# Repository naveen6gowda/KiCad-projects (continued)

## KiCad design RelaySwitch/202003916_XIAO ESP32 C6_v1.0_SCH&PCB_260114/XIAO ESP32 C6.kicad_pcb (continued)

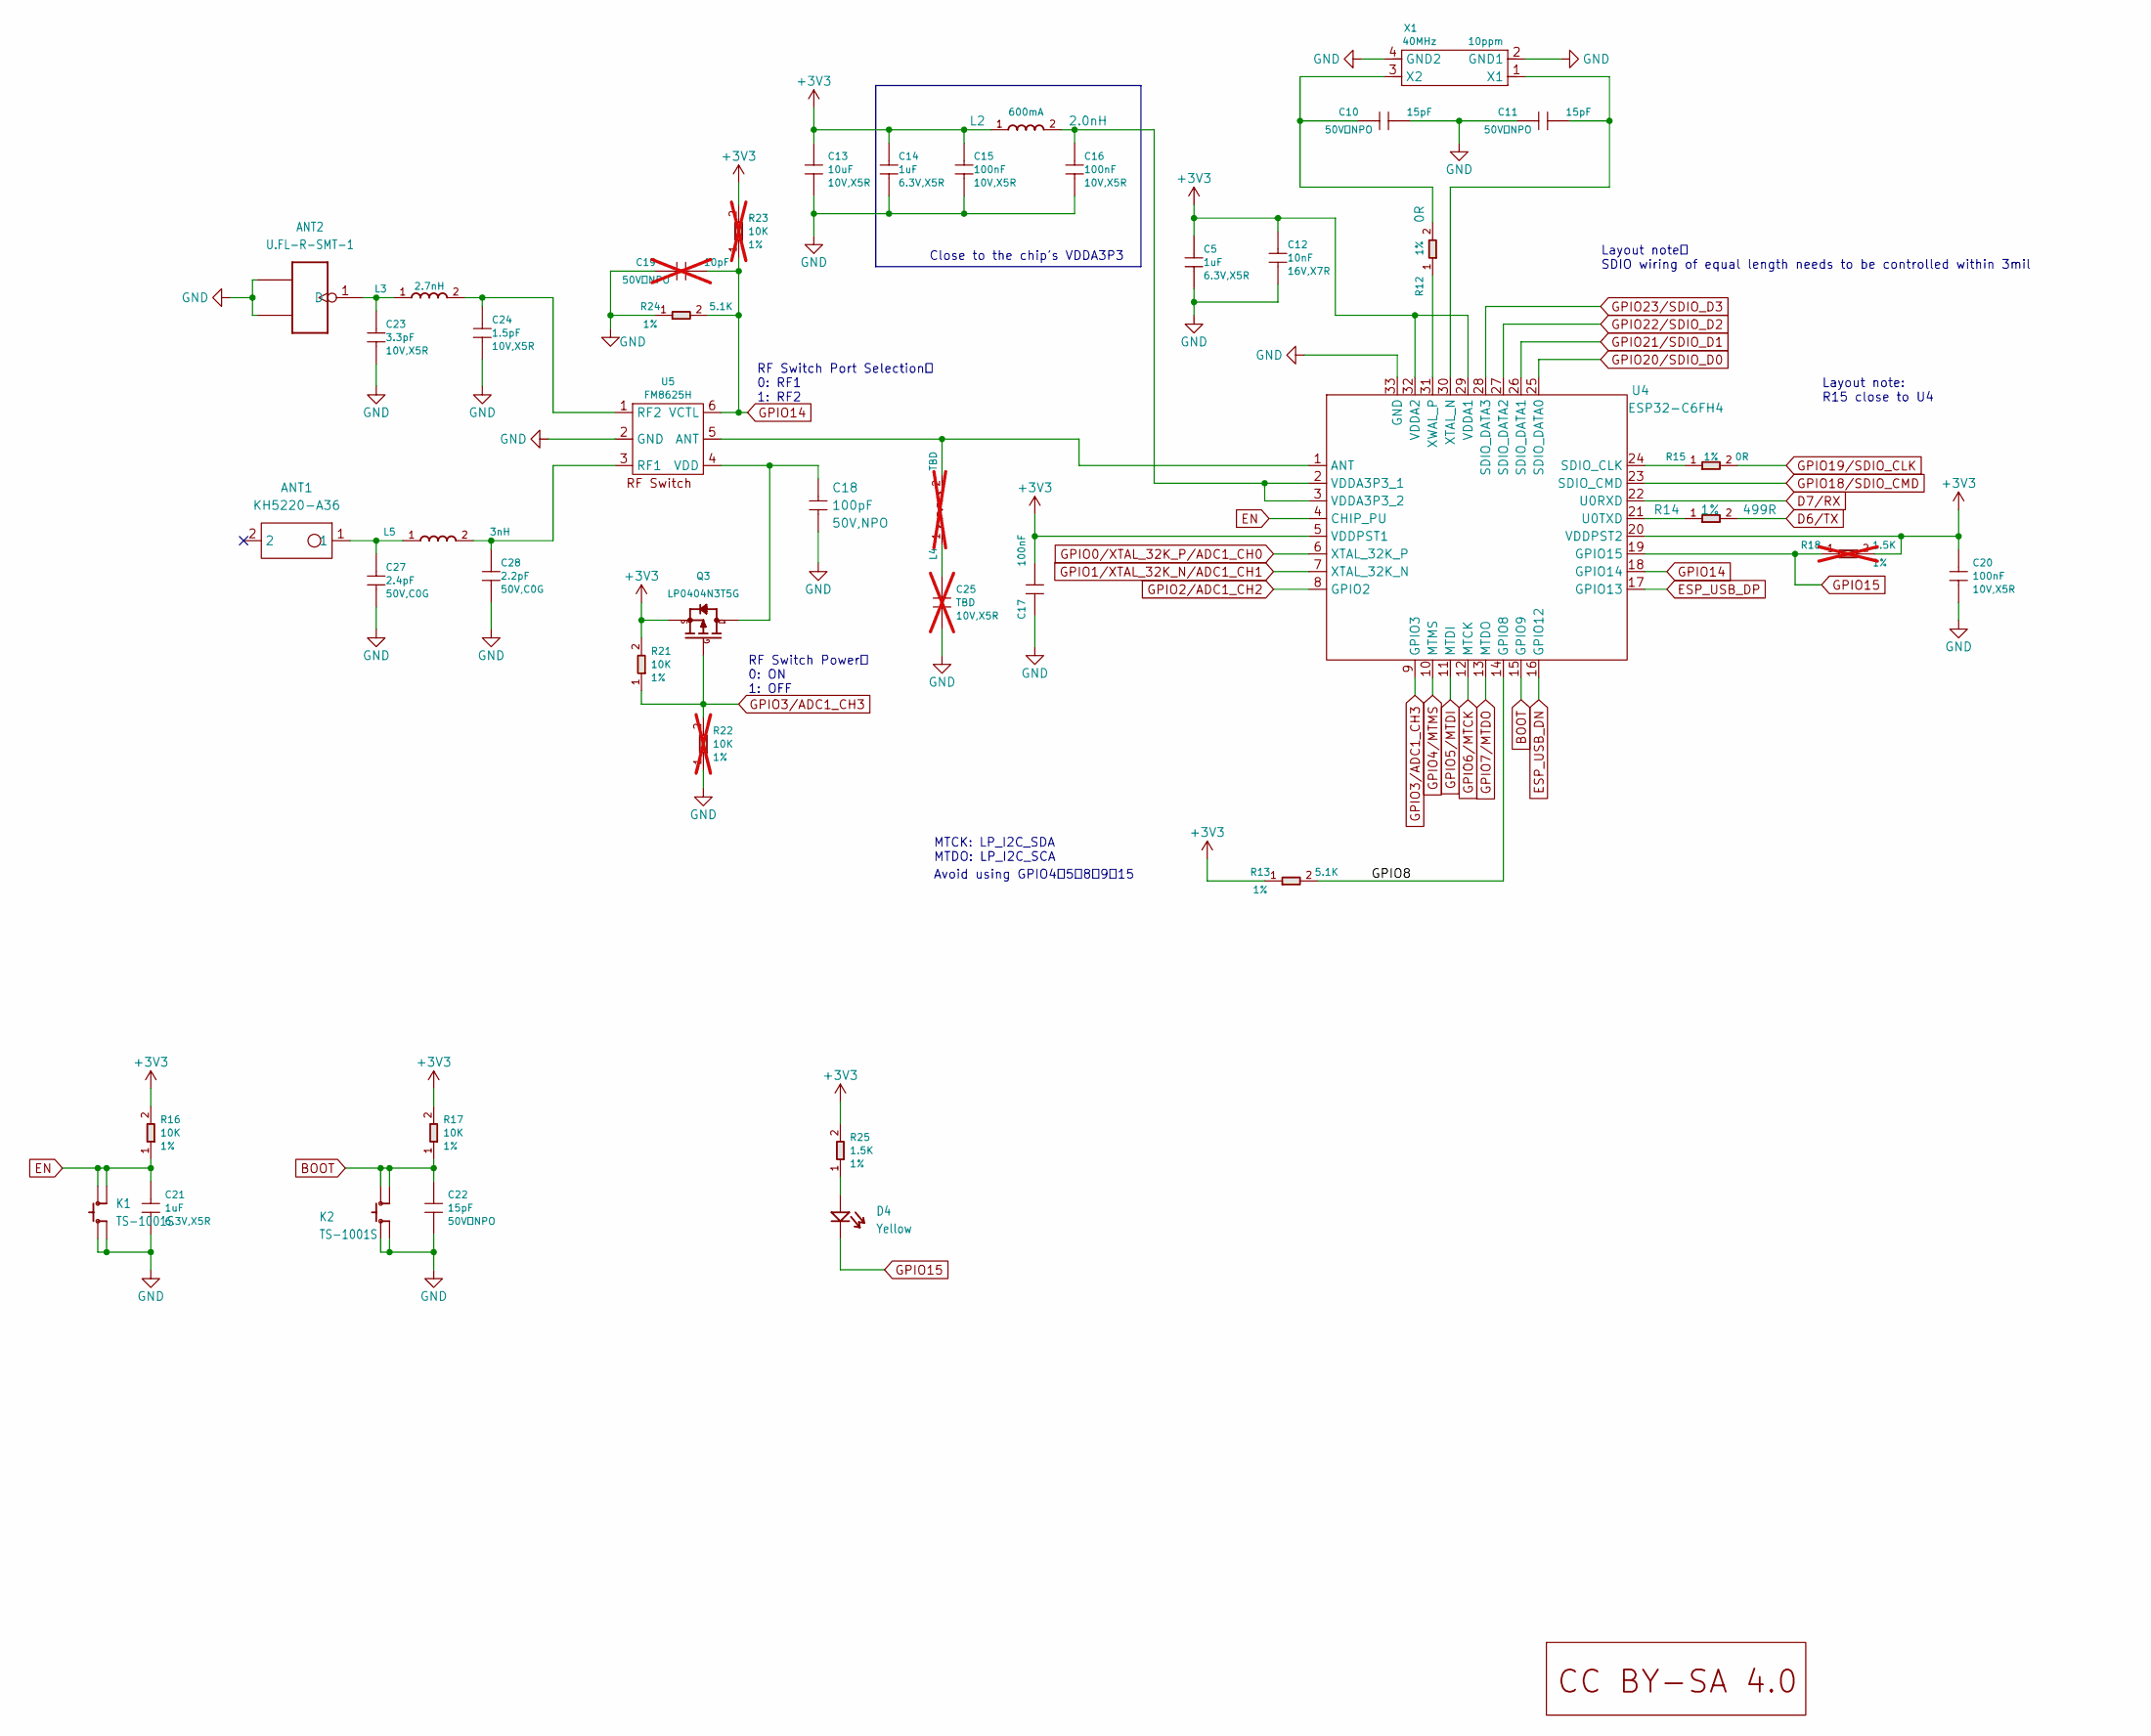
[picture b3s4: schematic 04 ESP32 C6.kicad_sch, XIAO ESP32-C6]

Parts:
ANT1: KH5220-A36; ANT2P-5.2x2x1.1MM; MPN KH5220-A36
ANT2: U.FL-R-SMT-1; U-FL3P-SMD-2.6X2.6X1.0MM; MPN U.FL-R-SMT-1
C5, C14, C21: 1uF; C0201; Voltage Rating 6.3V,X5R; MPN CC0201MRX5R5BB105
C10, C11, C22: 15pF; C0201; Voltage Rating 50V，NPO; MPN CC0201JRNPO9BN150
C12: 10nF; C0201; Voltage Rating 16V,X7R; MPN CC0201KRX7R7BB103
C13: 10uF; C0402; Voltage Rating 10V,X5R; MPN CC0402MRX5R6BB106
C15, C16, C17, C20: 100nF; C0201; Voltage Rating 10V,X5R; MPN CC0201KRX5R6BB104
C18: 100pF; C0201; Voltage Rating 50V,NPO; MPN CC0201JRNPO9BN101
C19: 10pF; C0201; Voltage Rating 50V，NPO; MPN CC0201JRNPO8BN100; not fitted
C23: 3.3pF; C0201; Voltage Rating 10V,X5R; MPN CQ0201BRNPO8BN3R3
C24: 1.5pF; C0201; Voltage Rating 10V,X5R; MPN CC0201BRNPO9BN1R5
C25: TBD; C0201; Voltage Rating 10V,X5R; Part Type Ceramic; not fitted
C27: 2.4pF; C0201; Voltage Rating 50V,C0G; MPN GRM0335C1H2R4BA01D
C28: 2.2pF; C0201; Voltage Rating 50V,C0G; MPN GRM0335C1H2R2BA01D
D4: Yellow; LED-0402; MPN 16-213/Y2C-AN2Q1B/3T
K1, K2: TS-1001S; SW4-SMD-2.8-2.6X1.6X0.53MM; MPN TS-1001S
L2: 2.0nH; L0201; Rating 600mA; MPN LQP03HQ2N0B02D
L3: 2.7nH; L0201; MPN LQP03TN2N7B02D
L4: TBD; L0201; Part Type L; not fitted
L5: 3nH; L0201; MPN LQP03TN3N0B02D
Q3: LP0404N3T5G; PMOS_1.0X0.6X0.35MM; MPN LP0404N3T5G
R12, R15: 0R; R0201; Power Rating 1%; MPN RC0201FR-070RL
R13, R24: 5.1K; R0201; Power Rating 1%; MPN RC0201FR-075K1L
R14: 499R; R0201; Power Rating 1%; MPN RC0201FR-07499RL
R16, R17, R21: 10K; R0201; Power Rating 1%; MPN RC0201FR-0710KL
R18: 1.5K; R0201; Power Rating 1%; MPN RC0201FR-071K5L; not fitted
R22, R23: 10K; R0201; Power Rating 1%; MPN RC0201FR-0710KL; not fitted
R25: 1.5K; R0201; Power Rating 1%; MPN RC0201FR-071K5L
U4: ESP32-C6FH4; QFN32-0.5-5X5MM; MPN ESP32-C6FH4
U5: FM8625H; DFN6-0.4-1.1X0.7X0.45MM; MPN FM8625H
U10: LOGO_CC_BY-SA_4.0
X1: 40MHz; X4-SMD-1.6X1.2MM; Rating 10ppm; MPN CJ17-400001010B20

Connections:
+3V3: C5.1, C12.1, C13.1, C14.1, C15.1, C17.1, C20.1, L2.1, Q3.2 (S), R13.1, R16.2, R17.2, R18.2, R21.2, R23.2, R25.2, U4.5 (VDDPST1), U4.20 (VDDPST2), U4.29 (VDDA1), U4.32 (VDDA2); also elsewhere on the board
/04 ESP32 C6/GPIO8: R13.2, U4.14 (GPIO8)
BOOT: C22.1, K2.3 (B0), K2.4 (B1), R17.1, U4.15 (GPIO9); also elsewhere on the board
D6/TX: R14.2; also elsewhere on the board
D7/RX: U4.22 (U0RXD); also elsewhere on the board
EN: C21.1, K1.3 (B0), K1.4 (B1), R16.1, U4.4 (CHIP_PU); also elsewhere on the board
ESP_USB_DN: U4.16 (GPIO12); also elsewhere on the board
ESP_USB_DP: U4.17 (GPIO13); also elsewhere on the board
GND: ANT2.2 (GND1), ANT2.3 (GND2), C5.2, C10.2, C11.1, C12.2, C13.2, C14.2, C15.2, C16.2, C17.2, C18.2, C19.1, C20.2, C21.2, C22.2, C23.2, C24.2, C25.2, C27.2, C28.2, K1.1 (A0), K1.2 (A1), K2.1 (A0), K2.2 (A1), R22.1, R24.1, U4.33 (GND), U5.2 (GND), X1.2 (GND1), X1.4 (GND2); also elsewhere on the board
GPIO0/XTAL_32K_P/ADC1_CH0: U4.6 (XTAL_32K_P); also elsewhere on the board
GPIO1/XTAL_32K_N/ADC1_CH1: U4.7 (XTAL_32K_N); also elsewhere on the board
GPIO2/ADC1_CH2: U4.8 (GPIO2); also elsewhere on the board
GPIO3/ADC1_CH3: Q3.1 (G), R21.1, R22.2, U4.9 (GPIO3)
GPIO4/MTMS: U4.10 (MTMS); also elsewhere on the board
GPIO5/MTDI: U4.11 (MTDI); also elsewhere on the board
GPIO6/MTCK: U4.12 (MTCK); also elsewhere on the board
GPIO7/MTDO: U4.13 (MTDO); also elsewhere on the board
GPIO14: C19.2, R23.1, R24.2, U4.18 (GPIO14), U5.6 (VCTL)
GPIO15: D4.2 (-), R18.1, U4.19 (GPIO15)
GPIO18/SDIO_CMD: U4.23 (SDIO_CMD); also elsewhere on the board
GPIO19/SDIO_CLK: R15.2; also elsewhere on the board
GPIO20/SDIO_D0: U4.25 (SDIO_DATA0); also elsewhere on the board
GPIO21/SDIO_D1: U4.26 (SDIO_DATA1); also elsewhere on the board
GPIO22/SDIO_D2: U4.27 (SDIO_DATA2); also elsewhere on the board
GPIO23/SDIO_D3: U4.28 (SDIO_DATA3); also elsewhere on the board
unnamed: ANT1.1, C27.1, L5.1
unnamed: ANT2.1 (D), C23.1, L3.1
unnamed: C25.1, L4.1
unnamed: D4.1 (+), R25.1
unnamed: C18.1, Q3.3 (D), U5.4 (VDD)
unnamed: L4.2, U4.1 (ANT), U5.5 (ANT)
unnamed: R15.1, U4.24 (SDIO_CLK)
unnamed: R14.1, U4.21 (U0TXD)
unnamed: C16.1, L2.2, U4.2 (VDDA3P3_1), U4.3 (VDDA3P3_2)
unnamed: C11.2, U4.30 (XTAL_N), X1.1 (X1)
unnamed: R12.1, U4.31 (XWAL_P)
unnamed: C28.1, L5.2, U5.3 (RF1)
unnamed: C24.1, L3.2, U5.1 (RF2)
unnamed: C10.1, R12.2, X1.3 (X2)

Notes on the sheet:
Avoid using GPIO4、5、8、9、15
RF Switch Power： 0: ON 1: OFF
Layout note: R15 close to U4
Close to the chip's VDDA3P3
Layout note： SDIO wiring of equal length needs to be controlled within 3mil
RF Switch Port Selection： 0: RF1 1: RF2
MTCK: LP_I2C_SDA MTDO: LP_I2C_SCA

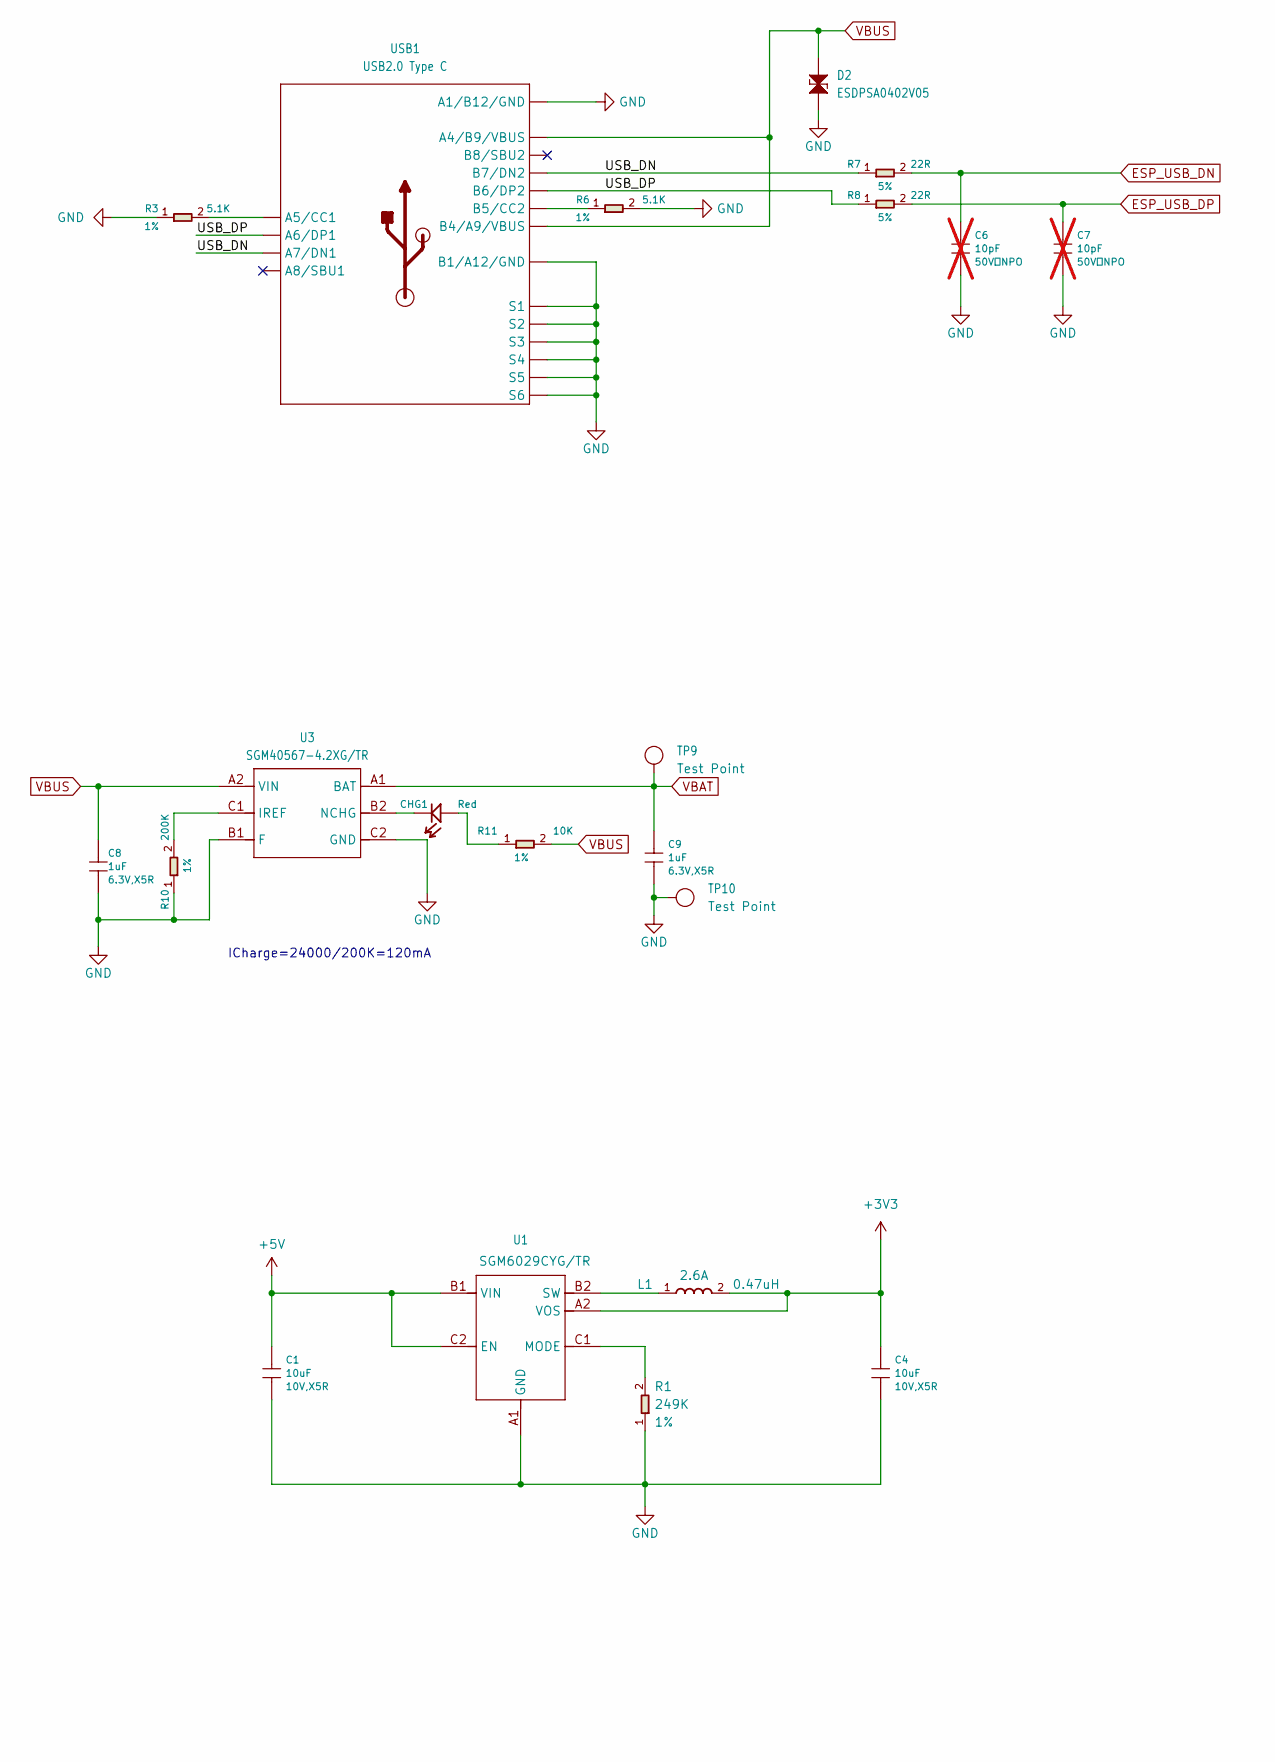
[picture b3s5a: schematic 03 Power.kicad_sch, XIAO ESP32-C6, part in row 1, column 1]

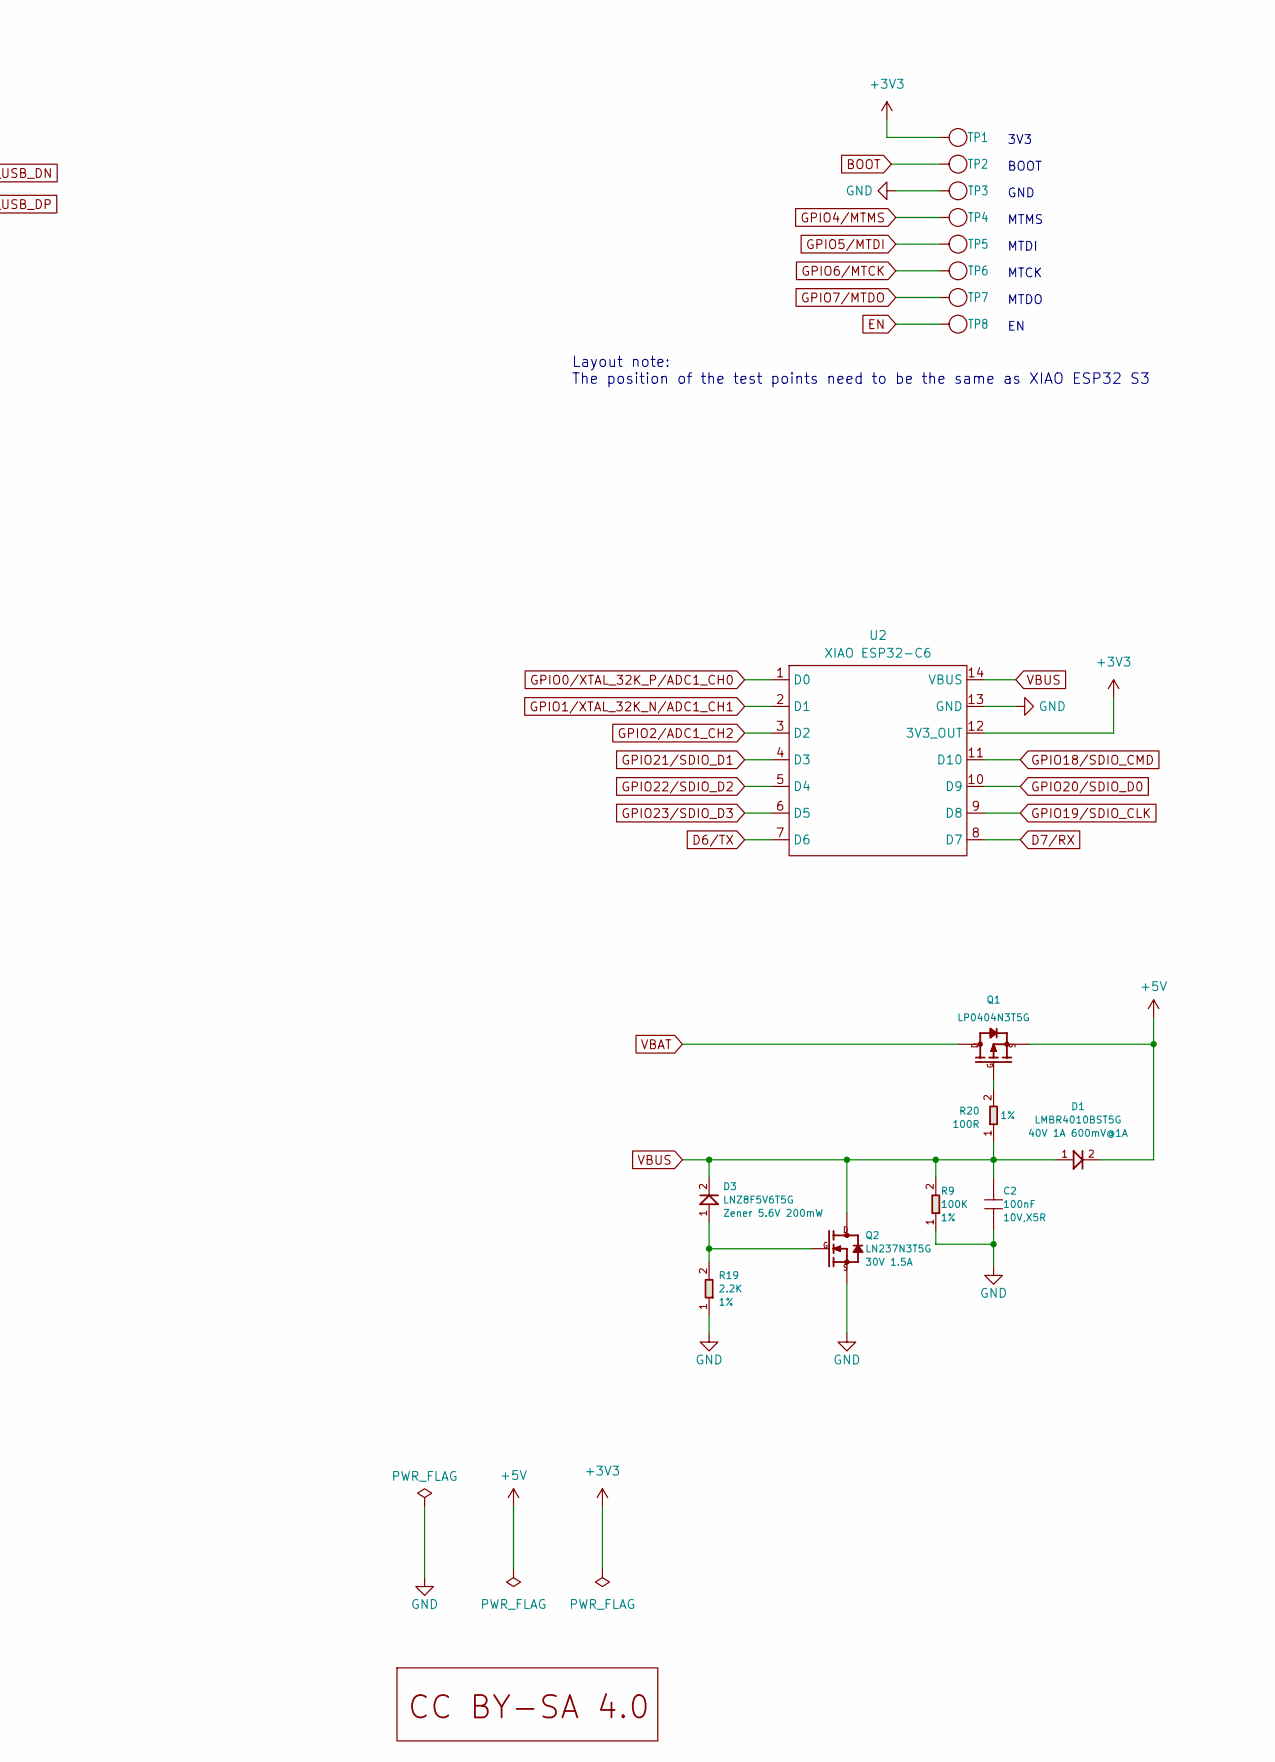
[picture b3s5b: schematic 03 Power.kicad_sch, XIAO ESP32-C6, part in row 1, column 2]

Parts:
C1, C4: 10uF; C0402; Voltage Rating 10V,X5R; MPN CC0402MRX5R6BB106
C2: 100nF; C0201; Voltage Rating 10V,X5R; MPN CC0201KRX5R6BB104
C6, C7: 10pF; C0201; Voltage Rating 50V，NPO; MPN CC0201JRNPO8BN100; not fitted
C8, C9: 1uF; C0201; Voltage Rating 6.3V,X5R; MPN CC0201MRX5R5BB105
CHG1: Red; LED-0402; MPN BL-HUB37A-AV-TRB
D1: LMBR4010BST5G; DFN1006-2L; Rating 40V 1A 600mV@1A; MPN LMBR4010BST5G
D2: ESDPSA0402V05; ESD-0402; MPN ESDPSA0402V05
D3: LNZ8F5V6T5G; DFN1006-2L; Rating Zener 5.6V 200mW; MPN LNZ8F5V6T5G
L1: 0.47uH; L0603; Rating 2.6A; MPN TFM160808ALC-R47MTAA
Q1: LP0404N3T5G; PMOS_1.0X0.6X0.35MM; MPN LP0404N3T5G
Q2: LN237N3T5G; PMOS_1.0X0.6X0.35MM; Rating 30V 1.5A; MPN LN237N3T5G
R1: 249K; R0201; Power Rating 1%; MPN RC0201FR-07249KL
R3, R6: 5.1K; R0201; Power Rating 1%; MPN RC0201FR-075K1L
R7, R8: 22R; R0201; Power Rating 5%; MPN RC0201JR-0722RL
R9: 100K; R0201; Power Rating 1%; MPN RC0201FR-07100KL
R10: 200K; R0201; Power Rating 1%; MPN RC0201FR-07200KL
R11: 10K; R0201; Power Rating 1%; MPN RC0201FR-0710KL
R19: 2.2K; R0201; Power Rating 1%; MPN RC0201FR-072K2L
R20: 100R; R0201; Power Rating 1%; MPN RC0201FR-07100RL
TP1, TP2, TP3, TP4, TP5, TP6, TP7, TP8: Test Point; TP-D45MIL; Part Type Test Point
TP9, TP10: Test Point; TP-80X40MIL; Part Type Test Point
U1: SMD IC PMIC;DCDC Buck-ADJ-1A,Vin 1.95V to 5.5V,Vo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; BGA6-0.35-0.745X10.95X0.4MM; MPN SGM6029CYG/TR
U2: XIAO ESP32-C6; XIAO-Add-On
U3: SGM40567-4.2XG/TR; WLCSP-0.4-0.92X1.16X0.4MM; MPN SGM40567-4.2XG/TR
U9: LOGO_CC_BY-SA_4.0
USB1: USB2.0 Type C; USB2.0-TYPE-C; MPN UBF31-0171

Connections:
+3V3: C4.1, L1.2, TP1.1 (T), U1.A2 (VOS), U2.12 (3V3); also elsewhere on the board
+5V: C1.1, D1.2, Q1.2 (S), U1.B1 (VIN), U1.C2 (EN)
/03 Power/USB_DN: R7.1, USB1.A7 (A7/DN1), USB1.B7 (B7/DN2)
/03 Power/USB_DP: R8.1, USB1.A6 (A6/DP1), USB1.B6 (B6/DP2)
BOOT: TP2.1 (T); also elsewhere on the board
D6/TX: U2.7 (PB08_A6_D6_TX); also elsewhere on the board
D7/RX: U2.8 (PB09_A7_D7_RX); also elsewhere on the board
EN: TP8.1 (T); also elsewhere on the board
ESP_USB_DN: C6.1, R7.2; also elsewhere on the board
ESP_USB_DP: C7.1, R8.2; also elsewhere on the board
GND: C1.2, C2.2, C4.2, C6.2, C7.2, C8.2, C9.2, D2.1, Q2.2 (S), R1.1, R3.1, R6.2, R9.1, R10.1, R19.1, TP3.1 (T), TP10.1 (T), U1.A1 (GND), U2.13 (GND), U3.B1 (F), U3.C2 (GND), USB1.A1_B12 (A1/B12/GND), USB1.B1_A12 (B1/A12/GND), USB1.S1, USB1.S2, USB1.S3, USB1.S4, USB1.S5, USB1.S6; also elsewhere on the board
GPIO0/XTAL_32K_P/ADC1_CH0: U2.1 (PA02_A0_D0); also elsewhere on the board
GPIO1/XTAL_32K_N/ADC1_CH1: U2.2 (PA4_A1_D1); also elsewhere on the board
GPIO2/ADC1_CH2: U2.3 (PA10_A2_D2); also elsewhere on the board
GPIO4/MTMS: TP4.1 (T); also elsewhere on the board
GPIO5/MTDI: TP5.1 (T); also elsewhere on the board
GPIO6/MTCK: TP6.1 (T); also elsewhere on the board
GPIO7/MTDO: TP7.1 (T); also elsewhere on the board
GPIO18/SDIO_CMD: U2.11 (PA6_A10_D10_MOSI); also elsewhere on the board
GPIO19/SDIO_CLK: U2.9 (PA7_A8_D8_SCK); also elsewhere on the board
GPIO20/SDIO_D0: U2.10 (PA5_A9_D9_MISO); also elsewhere on the board
GPIO21/SDIO_D1: U2.4 (PA11_A3_D3); also elsewhere on the board
GPIO22/SDIO_D2: U2.5 (PA8_A4_D4_SDA); also elsewhere on the board
GPIO23/SDIO_D3: U2.6 (PA9_A5_D5_SCL); also elsewhere on the board
unnamed: CHG1.1 (+), R11.1
unnamed: CHG1.2 (-), U3.B2 (NCHG)
unnamed: Q1.1 (G), R20.2
unnamed: D3.1, Q2.1 (G), R19.2
unnamed: R1.2, U1.C1 (MODE)
unnamed: L1.1, U1.B2 (SW)
unnamed: R10.2, U3.C1 (IREF)
unnamed: R3.2, USB1.A5 (A5/CC1)
unnamed: R6.1, USB1.B5 (B5/CC2)
VBAT: C9.1, Q1.3 (D), TP9.1 (T), U3.A1 (BAT)
VBUS: C2.1, C8.1, D1.1, D2.2, D3.2, Q2.3 (D), R9.2, R11.2, R20.1, U2.14 (5V), U3.A2 (VIN), USB1.A4_B9 (A4/B9/VBUS), USB1.B4_A9 (B4/A9/VBUS)

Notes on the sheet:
MTMS
MTDI
ICharge=24000/200K=120mA
GND
MTDO
Layout note: The position of the test points need to be the same as XIAO ESP32 S3
MTCK
BOOT
3V3

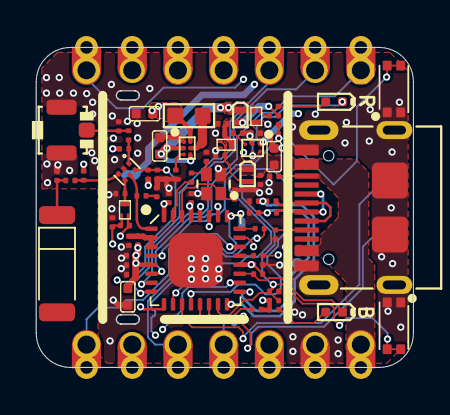
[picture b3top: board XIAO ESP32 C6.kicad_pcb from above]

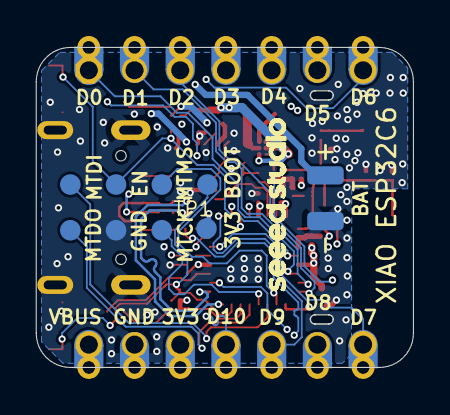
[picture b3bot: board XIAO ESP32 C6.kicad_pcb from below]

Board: 4 copper layers, 21.0 x 17.8 mm, 82 parts (10 on the bottom side), 53 nets.

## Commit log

2026-03-06 Initial commit - KiCad projects
2026-03-07 07/03
2026-03-08 Reduced relay size
2026-03-09 For review
2026-03-09 Review with borad extended
2026-03-11 warning fix - 17 left
2026-03-11 warning fix - 0 in schematic
2026-03-12 Fixed relay connections and F1 Fuse
2026-03-14 relay after layout design
2026-03-16 Complete layout
2026-03-19 replaced the Q1 and 2 with Dual driver
2026-03-20 Revert CM5_MINIMA_REV3-main to pre-warning-fix state (feae2c2) - fix component mismatches
2026-03-20 with old version retraced and fixing
